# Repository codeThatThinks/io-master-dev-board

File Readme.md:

# io-master-dev-board

A dev board for continuing development of the I/O Master.

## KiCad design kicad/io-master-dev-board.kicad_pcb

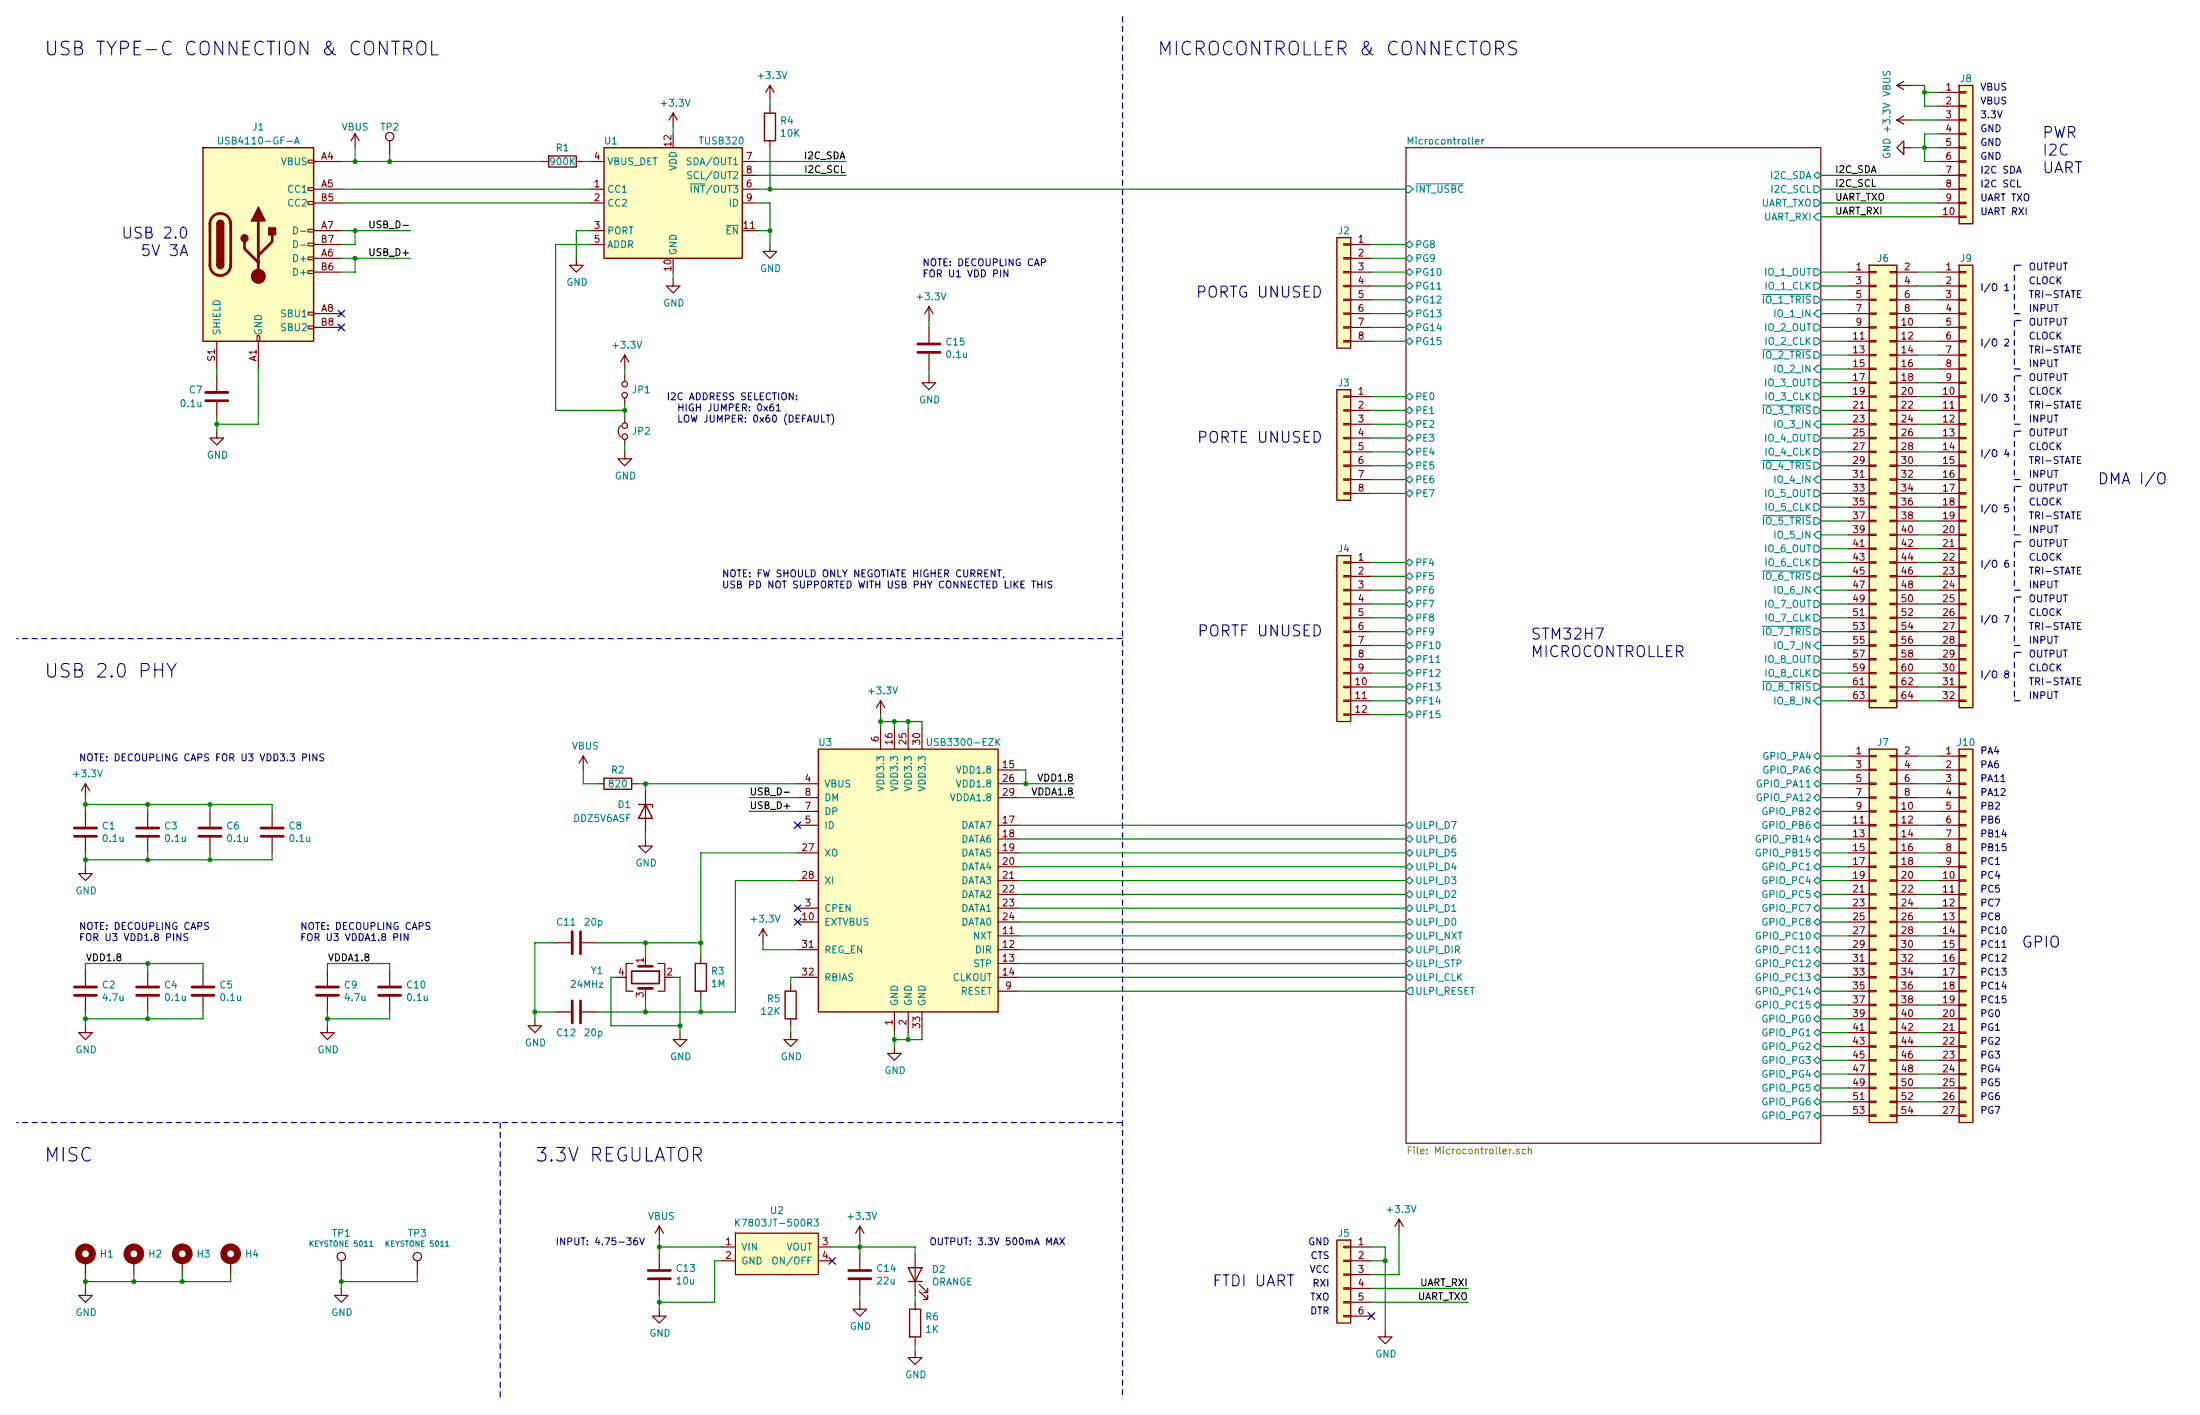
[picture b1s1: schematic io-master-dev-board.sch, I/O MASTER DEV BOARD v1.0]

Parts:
C1, C3, C4, C5, C6, C7, C8, C10, C15: 0.1u; C_0603_1608Metric
C2, C9: 4.7u; C_0805_2012Metric
C11, C12: 20p; C_0603_1608Metric
C13: 10u; C_0805_2012Metric
C14: 22u; C_1210_3225Metric
D1: DDZ5V6ASF; D_SOD-323F
D2: ORANGE; LED_0603_1608Metric
H1, H2, H3, H4: M3; MountingHole_3.2mm_M3_Pad
J1: USB4110-GF-A; USB_C_Receptable_GCT_USB4110
J2, J3: Conn_01x08; PinHeader_1x08_P2.54mm_Vertical
J4: Conn_01x12; PinHeader_1x12_P2.54mm_Vertical
J5: UART; PinHeader_1x06_P2.54mm_Horizontal
J6: Conn_02x32_Odd_Even; PinHeader_2x32_P1.27mm_Vertical
J7: Conn_02x27_Odd_Even; PinHeader_2x27_P1.27mm_Vertical
J8: Conn_01x10; PinHeader_1x10_P1.27mm_Vertical
J9: Conn_01x32; PinHeader_1x32_P1.27mm_Vertical
J10: Conn_01x27; PinHeader_1x27_P1.27mm_Vertical
JP1: Jumper_NO_Small; R_0603_1608Metric
JP2: Jumper_NC_Small; R_0603_1608Metric
R1: 900K; R_0603_1608Metric
R2: 820; R_0603_1608Metric
R3: 1M; R_0603_1608Metric
R4: 10K; R_0603_1608Metric
R5: 12K; R_0603_1608Metric
R6: 1K; R_0603_1608Metric
TP1, TP3: GND; TestPoint_Keystone_5010-5014_Multipurpose
TP2: VBUS; TestPoint_Pad_D1.0mm
U1: TUSB320; Texas_X2QFN-12_1.6x1.6mm_P0.4mm
U2: K7803JT-500R3; DCDC_Module_K78xxJT-500R3
U3: USB3300-EZK; QFN-32-1EP_5x5mm_P0.5mm_EP3.45x3.45mm
Y1: 24MHz; Crystal_SMD_Murata_XRCGB

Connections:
+3V3: C1.1, C3.1, C6.1, C8.1, C14.1, C15.1, D2.2 (A), J5.3, J8.3, JP1.2, R4.1, U1.12 (VDD), U2.3 (VOUT), U3.6 (VDD3.3), U3.16 (VDD3.3), U3.25 (VDD3.3), U3.30 (VDD3.3), U3.31 (REG_EN); also elsewhere on the board
/I2C_SCL: J8.8, U1.8 (SCL/OUT2); also elsewhere on the board
/I2C_SDA: J8.7, U1.7 (SDA/OUT1); also elsewhere on the board
/Microcontroller/GPIO_PA4: J7.1; also elsewhere on the board
/Microcontroller/GPIO_PA6: J7.3; also elsewhere on the board
/Microcontroller/GPIO_PA11: J7.5; also elsewhere on the board
/Microcontroller/GPIO_PA12: J7.7; also elsewhere on the board
/Microcontroller/GPIO_PB2: J7.9; also elsewhere on the board
/Microcontroller/GPIO_PB6: J7.11; also elsewhere on the board
/Microcontroller/GPIO_PB14: J7.13; also elsewhere on the board
/Microcontroller/GPIO_PB15: J7.15; also elsewhere on the board
/Microcontroller/GPIO_PC1: J7.17; also elsewhere on the board
/Microcontroller/GPIO_PC4: J7.19; also elsewhere on the board
/Microcontroller/GPIO_PC5: J7.21; also elsewhere on the board
/Microcontroller/GPIO_PC7: J7.23; also elsewhere on the board
/Microcontroller/GPIO_PC8: J7.25; also elsewhere on the board
/Microcontroller/GPIO_PC10: J7.27; also elsewhere on the board
/Microcontroller/GPIO_PC11: J7.29; also elsewhere on the board
/Microcontroller/GPIO_PC12: J7.31; also elsewhere on the board
/Microcontroller/GPIO_PC13: J7.33; also elsewhere on the board
/Microcontroller/GPIO_PC14: J7.35; also elsewhere on the board
/Microcontroller/GPIO_PC15: J7.37; also elsewhere on the board
/Microcontroller/GPIO_PG0: J7.39; also elsewhere on the board
/Microcontroller/GPIO_PG1: J7.41; also elsewhere on the board
/Microcontroller/GPIO_PG2: J7.43; also elsewhere on the board
/Microcontroller/GPIO_PG3: J7.45; also elsewhere on the board
/Microcontroller/GPIO_PG4: J7.47; also elsewhere on the board
/Microcontroller/GPIO_PG5: J7.49; also elsewhere on the board
/Microcontroller/GPIO_PG6: J7.51; also elsewhere on the board
/Microcontroller/GPIO_PG7: J7.53; also elsewhere on the board
/Microcontroller/IO_1_CLK: J6.3; also elsewhere on the board
/Microcontroller/IO_1_IN: J6.7; also elsewhere on the board
/Microcontroller/IO_1_OUT: J6.1; also elsewhere on the board
/Microcontroller/IO_2_CLK: J6.11; also elsewhere on the board
/Microcontroller/IO_2_IN: J6.15; also elsewhere on the board
/Microcontroller/IO_2_OUT: J6.9; also elsewhere on the board
/Microcontroller/IO_3_CLK: J6.19; also elsewhere on the board
/Microcontroller/IO_3_IN: J6.23; also elsewhere on the board
/Microcontroller/IO_3_OUT: J6.17; also elsewhere on the board
/Microcontroller/IO_4_CLK: J6.27; also elsewhere on the board
/Microcontroller/IO_4_IN: J6.31; also elsewhere on the board
/Microcontroller/IO_4_OUT: J6.25; also elsewhere on the board
/Microcontroller/IO_5_CLK: J6.35; also elsewhere on the board
/Microcontroller/IO_5_IN: J6.39; also elsewhere on the board
/Microcontroller/IO_5_OUT: J6.33; also elsewhere on the board
/Microcontroller/IO_6_CLK: J6.43; also elsewhere on the board
/Microcontroller/IO_6_IN: J6.47; also elsewhere on the board
/Microcontroller/IO_6_OUT: J6.41; also elsewhere on the board
/Microcontroller/IO_7_CLK: J6.51; also elsewhere on the board
/Microcontroller/IO_7_IN: J6.55; also elsewhere on the board
/Microcontroller/IO_7_OUT: J6.49; also elsewhere on the board
/Microcontroller/IO_8_CLK: J6.59; also elsewhere on the board
/Microcontroller/IO_8_IN: J6.63; also elsewhere on the board
/Microcontroller/IO_8_OUT: J6.57; also elsewhere on the board
/Microcontroller/PE0: J3.1; also elsewhere on the board
/Microcontroller/PE1: J3.2; also elsewhere on the board
/Microcontroller/PE2: J3.3; also elsewhere on the board
/Microcontroller/PE3: J3.4; also elsewhere on the board
/Microcontroller/PE4: J3.5; also elsewhere on the board
/Microcontroller/PE5: J3.6; also elsewhere on the board
/Microcontroller/PE6: J3.7; also elsewhere on the board
/Microcontroller/PE7: J3.8; also elsewhere on the board
/Microcontroller/PF4: J4.1; also elsewhere on the board
/Microcontroller/PF5: J4.2; also elsewhere on the board
/Microcontroller/PF6: J4.3; also elsewhere on the board
/Microcontroller/PF7: J4.4; also elsewhere on the board
/Microcontroller/PF8: J4.5; also elsewhere on the board
/Microcontroller/PF9: J4.6; also elsewhere on the board
/Microcontroller/PF10: J4.7; also elsewhere on the board
/Microcontroller/PF11: J4.8; also elsewhere on the board
/Microcontroller/PF12: J4.9; also elsewhere on the board
/Microcontroller/PF13: J4.10; also elsewhere on the board
/Microcontroller/PF14: J4.11; also elsewhere on the board
/Microcontroller/PF15: J4.12; also elsewhere on the board
/Microcontroller/PG8: J2.1; also elsewhere on the board
/Microcontroller/PG9: J2.2; also elsewhere on the board
/Microcontroller/PG10: J2.3; also elsewhere on the board
/Microcontroller/PG11: J2.4; also elsewhere on the board
/Microcontroller/PG12: J2.5; also elsewhere on the board
/Microcontroller/PG13: J2.6; also elsewhere on the board
/Microcontroller/PG14: J2.7; also elsewhere on the board
/Microcontroller/PG15: J2.8; also elsewhere on the board
/Microcontroller/ULPI_CLK: U3.14 (CLKOUT); also elsewhere on the board
/Microcontroller/ULPI_D0: U3.24 (DATA0); also elsewhere on the board
/Microcontroller/ULPI_D1: U3.23 (DATA1); also elsewhere on the board
/Microcontroller/ULPI_D2: U3.22 (DATA2); also elsewhere on the board
/Microcontroller/ULPI_D3: U3.21 (DATA3); also elsewhere on the board
/Microcontroller/ULPI_D4: U3.20 (DATA4); also elsewhere on the board
/Microcontroller/ULPI_D5: U3.19 (DATA5); also elsewhere on the board
/Microcontroller/ULPI_D6: U3.18 (DATA6); also elsewhere on the board
/Microcontroller/ULPI_D7: U3.17 (DATA7); also elsewhere on the board
/Microcontroller/ULPI_DIR: U3.12 (DIR); also elsewhere on the board
/Microcontroller/ULPI_NXT: U3.11 (NXT); also elsewhere on the board
/Microcontroller/ULPI_RESET: U3.9 (RESET); also elsewhere on the board
/Microcontroller/ULPI_STP: U3.13 (STP); also elsewhere on the board
/Microcontroller/~INT_USBC: R4.2, U1.6 (~INT~/OUT3); also elsewhere on the board
/Microcontroller/~IO_1_TRIS: J6.5; also elsewhere on the board
/Microcontroller/~IO_2_TRIS: J6.13; also elsewhere on the board
/Microcontroller/~IO_3_TRIS: J6.21; also elsewhere on the board
/Microcontroller/~IO_4_TRIS: J6.29; also elsewhere on the board
/Microcontroller/~IO_5_TRIS: J6.37; also elsewhere on the board
/Microcontroller/~IO_6_TRIS: J6.45; also elsewhere on the board
/Microcontroller/~IO_7_TRIS: J6.53; also elsewhere on the board
/Microcontroller/~IO_8_TRIS: J6.61; also elsewhere on the board
/UART_RXI: J5.4, J8.10; also elsewhere on the board
/UART_TXO: J5.5, J8.9; also elsewhere on the board
/USB_D+: J1.A6 (D+), J1.B6 (D+), U3.7 (DP)
/USB_D-: J1.A7 (D-), J1.B7 (D-), U3.8 (DM)
/VDD1.8: C2.1, C4.1, C5.1, U3.15 (VDD1.8), U3.26 (VDD1.8)
/VDDA1.8: C9.1, C10.1, U3.29 (VDDA1.8)
GND: C1.2, C2.2, C3.2, C4.2, C5.2, C6.2, C7.1, C8.2, C9.2, C10.2, C11.2, C12.2, C13.2, C14.2, C15.2, D1.2 (A), H1.1, H2.1, H3.1, H4.1, J1.A1 (GND), J1.A12 (GND), J1.B1 (GND), J1.B12 (GND), J5.1, J5.2, J8.4, J8.5, J8.6, JP2.1, R5.2, R6.2, TP1.1, TP3.1, U1.3 (PORT), U1.9 (ID), U1.10 (GND), U1.11 (~EN), U2.2 (GND), U3.1 (GND), U3.2 (GND), U3.33 (GND), Y1.2, Y1.4; also elsewhere on the board
unnamed: C7.2, J1.S1 (SHIELD)
unnamed: C11.1, R3.1, U3.27 (XO), Y1.1
unnamed: C12.1, R3.2, U3.28 (XI), Y1.3
unnamed: D1.1 (K), R2.1, U3.4 (VBUS)
unnamed: D2.1 (K), R6.1
unnamed: J1.A5 (CC1), U1.1 (CC1)
unnamed: J1.B5 (CC2), U1.2 (CC2)
unnamed: J6.2, J9.1
unnamed: J6.4, J9.2
unnamed: J6.6, J9.3
unnamed: J6.8, J9.4
unnamed: J6.10, J9.5
unnamed: J6.12, J9.6
unnamed: J6.14, J9.7
unnamed: J6.16, J9.8
unnamed: J6.18, J9.9
unnamed: J6.20, J9.10
unnamed: J6.22, J9.11
unnamed: J6.24, J9.12
unnamed: J6.26, J9.13
unnamed: J6.28, J9.14
unnamed: J6.30, J9.15
unnamed: J6.32, J9.16
unnamed: J6.34, J9.17
unnamed: J6.36, J9.18
unnamed: J6.38, J9.19
unnamed: J6.40, J9.20
unnamed: J6.42, J9.21
unnamed: J6.44, J9.22
unnamed: J6.46, J9.23
unnamed: J6.48, J9.24
unnamed: J6.50, J9.25
unnamed: J6.52, J9.26
unnamed: J6.54, J9.27
unnamed: J6.56, J9.28
unnamed: J6.58, J9.29
unnamed: J6.60, J9.30
unnamed: J6.62, J9.31
unnamed: J6.64, J9.32
unnamed: J7.2, J10.1
unnamed: J7.4, J10.2
unnamed: J7.6, J10.3
unnamed: J7.8, J10.4
unnamed: J7.10, J10.5
unnamed: J7.12, J10.6
unnamed: J7.14, J10.7
unnamed: J7.16, J10.8
unnamed: J7.18, J10.9
unnamed: J7.20, J10.10
unnamed: J7.22, J10.11
unnamed: J7.24, J10.12
unnamed: J7.26, J10.13
unnamed: J7.28, J10.14
unnamed: J7.30, J10.15
unnamed: J7.32, J10.16
unnamed: J7.34, J10.17
unnamed: J7.36, J10.18
unnamed: J7.38, J10.19
unnamed: J7.40, J10.20
unnamed: J7.42, J10.21
unnamed: J7.44, J10.22
unnamed: J7.46, J10.23
unnamed: J7.48, J10.24
unnamed: J7.50, J10.25
unnamed: J7.52, J10.26
unnamed: J7.54, J10.27
unnamed: JP1.1, JP2.2, U1.5 (ADDR)
unnamed: R1.1, U1.4 (VBUS_DET)
unnamed: R5.1, U3.32 (RBIAS)
VBUS: C13.1, J1.A4 (VBUS), J1.A9 (VBUS), J1.B4 (VBUS), J1.B9 (VBUS), J8.1, J8.2, R1.2, R2.2, TP2.1, U2.1 (VIN)

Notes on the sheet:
NOTE: DECOUPLING CAPS FOR U3 VDD1.8 PINS
NOTE: DECOUPLING CAPS FOR U3 VDD3.3 PINS
NOTE: DECOUPLING CAPS FOR U3 VDDA1.8 PIN
USB TYPE-C CONNECTION & CONTROL
USB 2.0 5V 3A
3.3V REGULATOR
I2C ADDRESS SELECTION: HIGH JUMPER: 0x61 LOW JUMPER: 0x60 (DEFAULT)
NOTE: DECOUPLING CAP FOR U1 VDD PIN
INPUT: 4.75-36V
OUTPUT: 3.3V 500mA MAX
STM32H7 MICROCONTROLLER
USB 2.0 PHY
MISC
MICROCONTROLLER & CONNECTORS
PWR I2C UART
DMA I/O
VBUS
3.3V
GND
I2C SDA
I2C SCL
UART TXO
UART RXI
I/O 1
OUTPUT
CLOCK
TRI-STATE
INPUT
I/O 2
I/O 3
I/O 4
I/O 5
I/O 6
I/O 7
I/O 8
GPIO
PA4
PA6
PA11
PA12

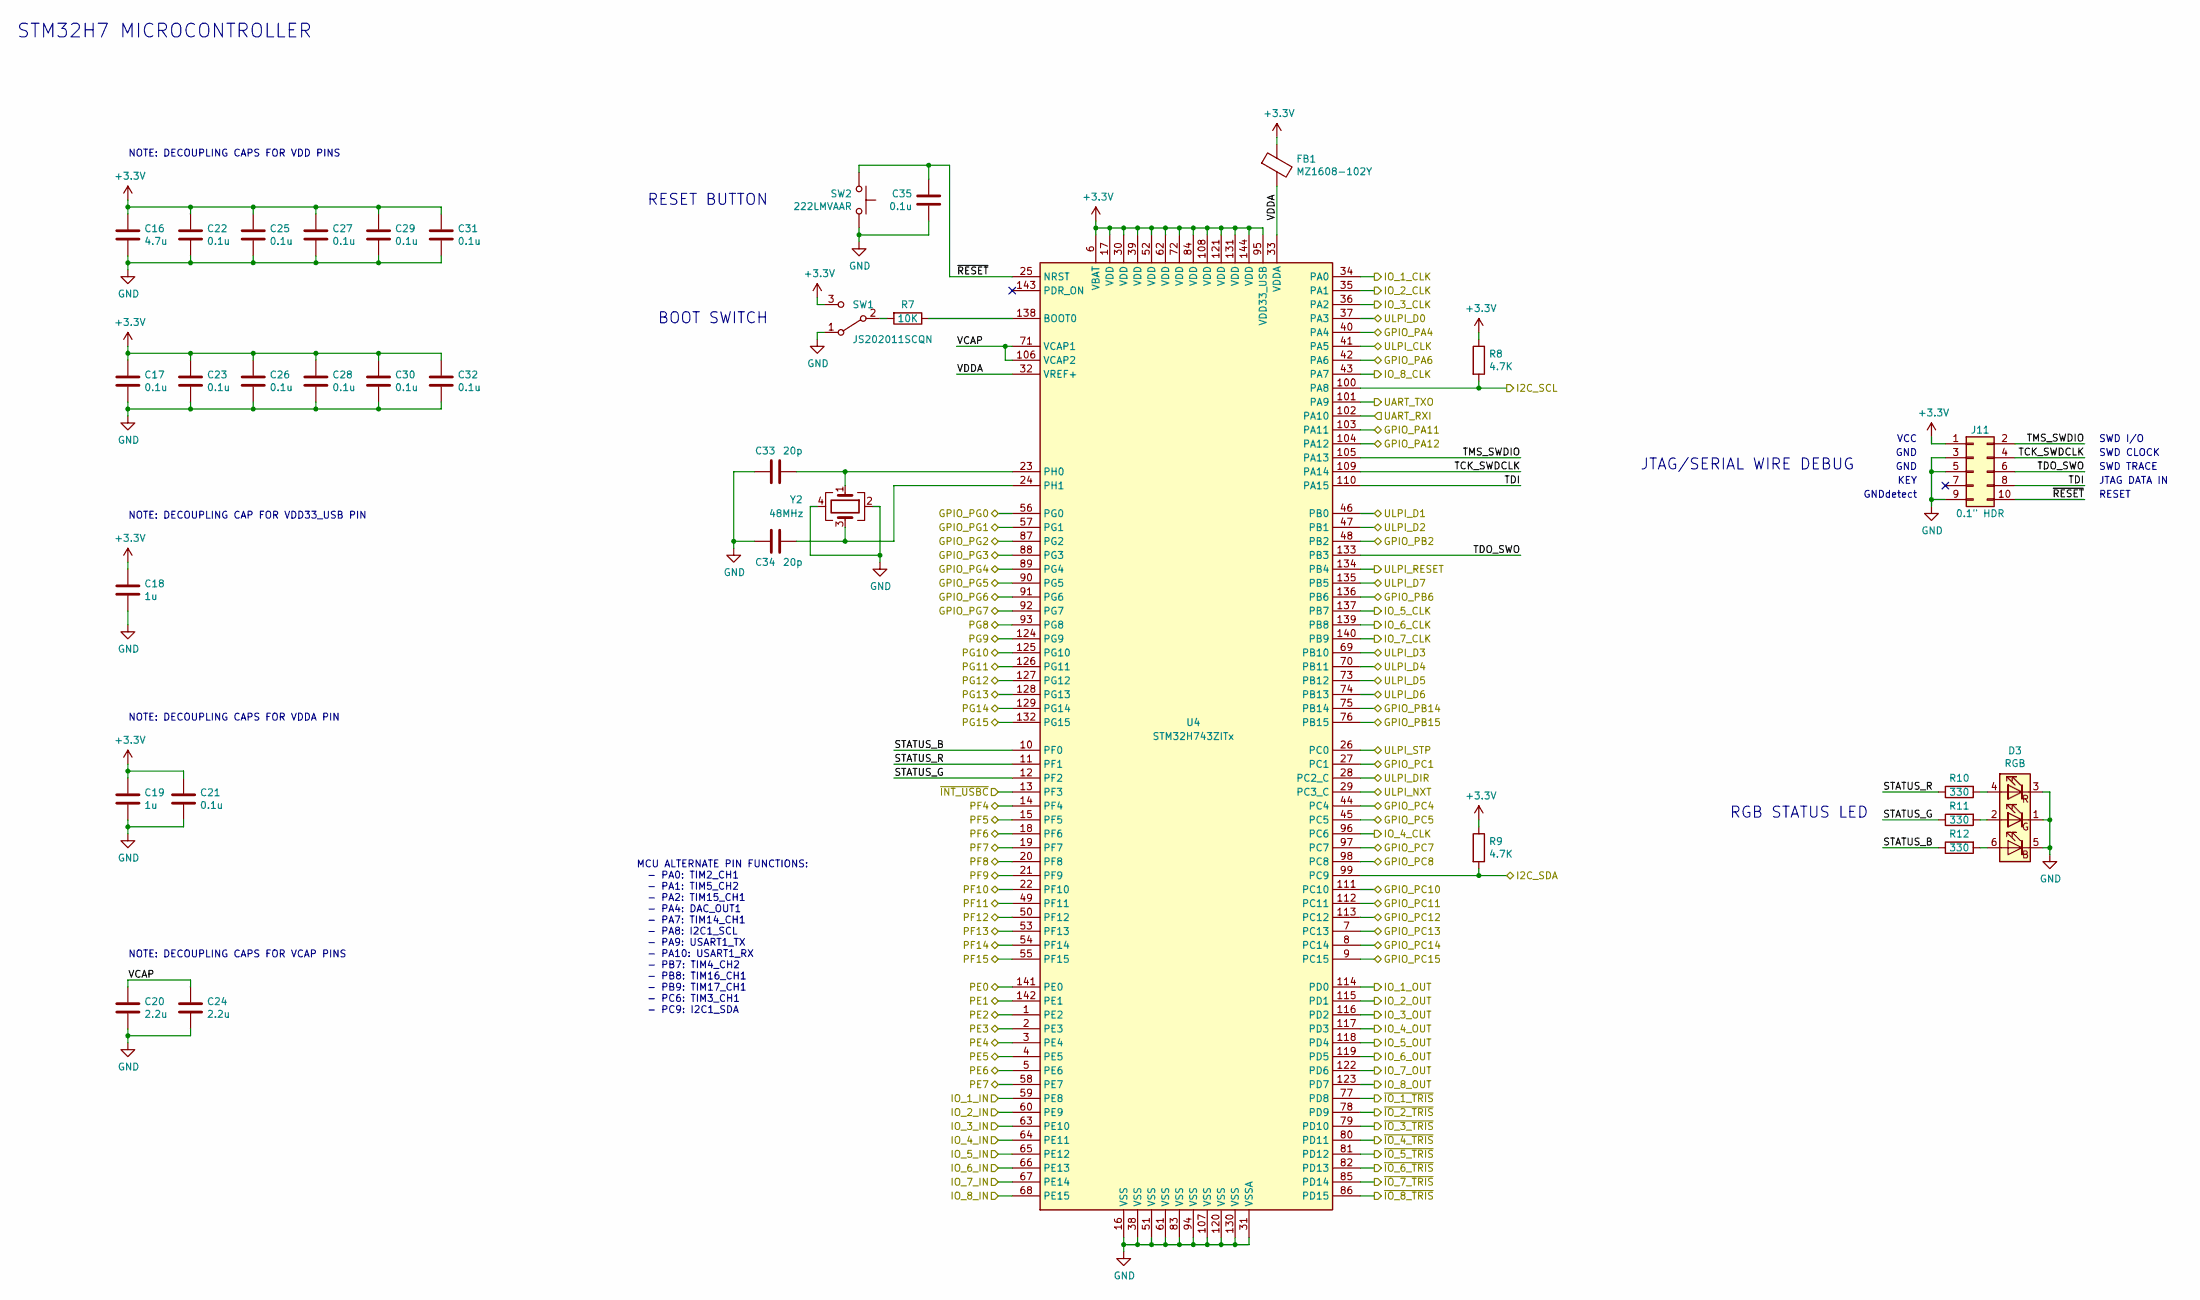
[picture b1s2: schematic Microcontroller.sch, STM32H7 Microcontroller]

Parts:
C16: 4.7u; C_0805_2012Metric
C17, C21, C22, C23, C25, C26, C27, C28, C29, C30, C31, C32, C35: 0.1u; C_0603_1608Metric
C18, C19: 1u; C_0603_1608Metric
C20, C24: 2.2u; C_0805_2012Metric
C33, C34: 20p; C_0603_1608Metric
D3: RGB; LED_Everlight_19-337C
FB1: MZ1608-102Y; R_0603_1608Metric
J11: 0.1\" HDR; PinSocket_2x05_P2.54mm_Vertical
R7: 10K; R_0603_1608Metric
R8, R9: 4.7K; R_0603_1608Metric
R10, R11, R12: 330; R_0603_1608Metric
SW1: JS202011SCQN; SW_DPDT_CK_JS202011SCQN
SW2: 222LMVAAR; SW_Push_CTS_222LMVA
U4: STM32H743ZITx; LQFP-144_20x20mm_P0.5mm
Y2: 48MHz; Crystal_SMD_Murata_XRCGB

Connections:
+3V3: C16.1, C17.1, C18.1, C19.1, C21.1, C22.1, C23.1, C25.1, C26.1, C27.1, C28.1, C29.1, C30.1, C31.1, C32.1, FB1.1, J11.1, R8.1, R9.1, SW1.3 (C), U4.6 (VBAT), U4.17 (VDD), U4.30 (VDD), U4.39 (VDD), U4.52 (VDD), U4.62 (VDD), U4.72 (VDD), U4.84 (VDD), U4.95 (VDD33_USB), U4.108 (VDD), U4.121 (VDD), U4.131 (VDD), U4.144 (VDD); also elsewhere on the board
/I2C_SCL: R8.2, U4.100 (PA8); also elsewhere on the board
/I2C_SDA: R9.2, U4.99 (PC9); also elsewhere on the board
/Microcontroller/GPIO_PA4: U4.40 (PA4); also elsewhere on the board
/Microcontroller/GPIO_PA6: U4.42 (PA6); also elsewhere on the board
/Microcontroller/GPIO_PA11: U4.103 (PA11); also elsewhere on the board
/Microcontroller/GPIO_PA12: U4.104 (PA12); also elsewhere on the board
/Microcontroller/GPIO_PB2: U4.48 (PB2); also elsewhere on the board
/Microcontroller/GPIO_PB6: U4.136 (PB6); also elsewhere on the board
/Microcontroller/GPIO_PB14: U4.75 (PB14); also elsewhere on the board
/Microcontroller/GPIO_PB15: U4.76 (PB15); also elsewhere on the board
/Microcontroller/GPIO_PC1: U4.27 (PC1); also elsewhere on the board
/Microcontroller/GPIO_PC4: U4.44 (PC4); also elsewhere on the board
/Microcontroller/GPIO_PC5: U4.45 (PC5); also elsewhere on the board
/Microcontroller/GPIO_PC7: U4.97 (PC7); also elsewhere on the board
/Microcontroller/GPIO_PC8: U4.98 (PC8); also elsewhere on the board
/Microcontroller/GPIO_PC10: U4.111 (PC10); also elsewhere on the board
/Microcontroller/GPIO_PC11: U4.112 (PC11); also elsewhere on the board
/Microcontroller/GPIO_PC12: U4.113 (PC12); also elsewhere on the board
/Microcontroller/GPIO_PC13: U4.7 (PC13); also elsewhere on the board
/Microcontroller/GPIO_PC14: U4.8 (PC14); also elsewhere on the board
/Microcontroller/GPIO_PC15: U4.9 (PC15); also elsewhere on the board
/Microcontroller/GPIO_PG0: U4.56 (PG0); also elsewhere on the board
/Microcontroller/GPIO_PG1: U4.57 (PG1); also elsewhere on the board
/Microcontroller/GPIO_PG2: U4.87 (PG2); also elsewhere on the board
/Microcontroller/GPIO_PG3: U4.88 (PG3); also elsewhere on the board
/Microcontroller/GPIO_PG4: U4.89 (PG4); also elsewhere on the board
/Microcontroller/GPIO_PG5: U4.90 (PG5); also elsewhere on the board
/Microcontroller/GPIO_PG6: U4.91 (PG6); also elsewhere on the board
/Microcontroller/GPIO_PG7: U4.92 (PG7); also elsewhere on the board
/Microcontroller/IO_1_CLK: U4.34 (PA0); also elsewhere on the board
/Microcontroller/IO_1_IN: U4.59 (PE8); also elsewhere on the board
/Microcontroller/IO_1_OUT: U4.114 (PD0); also elsewhere on the board
/Microcontroller/IO_2_CLK: U4.35 (PA1); also elsewhere on the board
/Microcontroller/IO_2_IN: U4.60 (PE9); also elsewhere on the board
/Microcontroller/IO_2_OUT: U4.115 (PD1); also elsewhere on the board
/Microcontroller/IO_3_CLK: U4.36 (PA2); also elsewhere on the board
/Microcontroller/IO_3_IN: U4.63 (PE10); also elsewhere on the board
/Microcontroller/IO_3_OUT: U4.116 (PD2); also elsewhere on the board
/Microcontroller/IO_4_CLK: U4.96 (PC6); also elsewhere on the board
/Microcontroller/IO_4_IN: U4.64 (PE11); also elsewhere on the board
/Microcontroller/IO_4_OUT: U4.117 (PD3); also elsewhere on the board
/Microcontroller/IO_5_CLK: U4.137 (PB7); also elsewhere on the board
/Microcontroller/IO_5_IN: U4.65 (PE12); also elsewhere on the board
/Microcontroller/IO_5_OUT: U4.118 (PD4); also elsewhere on the board
/Microcontroller/IO_6_CLK: U4.139 (PB8); also elsewhere on the board
/Microcontroller/IO_6_IN: U4.66 (PE13); also elsewhere on the board
/Microcontroller/IO_6_OUT: U4.119 (PD5); also elsewhere on the board
/Microcontroller/IO_7_CLK: U4.140 (PB9); also elsewhere on the board
/Microcontroller/IO_7_IN: U4.67 (PE14); also elsewhere on the board
/Microcontroller/IO_7_OUT: U4.122 (PD6); also elsewhere on the board
/Microcontroller/IO_8_CLK: U4.43 (PA7); also elsewhere on the board
/Microcontroller/IO_8_IN: U4.68 (PE15); also elsewhere on the board
/Microcontroller/IO_8_OUT: U4.123 (PD7); also elsewhere on the board
/Microcontroller/PE0: U4.141 (PE0); also elsewhere on the board
/Microcontroller/PE1: U4.142 (PE1); also elsewhere on the board
/Microcontroller/PE2: U4.1 (PE2); also elsewhere on the board
/Microcontroller/PE3: U4.2 (PE3); also elsewhere on the board
/Microcontroller/PE4: U4.3 (PE4); also elsewhere on the board
/Microcontroller/PE5: U4.4 (PE5); also elsewhere on the board
/Microcontroller/PE6: U4.5 (PE6); also elsewhere on the board
/Microcontroller/PE7: U4.58 (PE7); also elsewhere on the board
/Microcontroller/PF4: U4.14 (PF4); also elsewhere on the board
/Microcontroller/PF5: U4.15 (PF5); also elsewhere on the board
/Microcontroller/PF6: U4.18 (PF6); also elsewhere on the board
/Microcontroller/PF7: U4.19 (PF7); also elsewhere on the board
/Microcontroller/PF8: U4.20 (PF8); also elsewhere on the board
/Microcontroller/PF9: U4.21 (PF9); also elsewhere on the board
/Microcontroller/PF10: U4.22 (PF10); also elsewhere on the board
/Microcontroller/PF11: U4.49 (PF11); also elsewhere on the board
/Microcontroller/PF12: U4.50 (PF12); also elsewhere on the board
/Microcontroller/PF13: U4.53 (PF13); also elsewhere on the board
/Microcontroller/PF14: U4.54 (PF14); also elsewhere on the board
/Microcontroller/PF15: U4.55 (PF15); also elsewhere on the board
/Microcontroller/PG8: U4.93 (PG8); also elsewhere on the board
/Microcontroller/PG9: U4.124 (PG9); also elsewhere on the board
/Microcontroller/PG10: U4.125 (PG10); also elsewhere on the board
/Microcontroller/PG11: U4.126 (PG11); also elsewhere on the board
/Microcontroller/PG12: U4.127 (PG12); also elsewhere on the board
/Microcontroller/PG13: U4.128 (PG13); also elsewhere on the board
/Microcontroller/PG14: U4.129 (PG14); also elsewhere on the board
/Microcontroller/PG15: U4.132 (PG15); also elsewhere on the board
/Microcontroller/STATUS_B: R12.1, U4.10 (PF0)
/Microcontroller/STATUS_G: R11.1, U4.12 (PF2)
/Microcontroller/STATUS_R: R10.1, U4.11 (PF1)
/Microcontroller/TCK_SWDCLK: J11.4, U4.109 (PA14)
/Microcontroller/TDI: J11.8, U4.110 (PA15)
/Microcontroller/TDO_SWO: J11.6, U4.133 (PB3)
/Microcontroller/TMS_SWDIO: J11.2, U4.105 (PA13)
/Microcontroller/ULPI_CLK: U4.41 (PA5); also elsewhere on the board
/Microcontroller/ULPI_D0: U4.37 (PA3); also elsewhere on the board
/Microcontroller/ULPI_D1: U4.46 (PB0); also elsewhere on the board
/Microcontroller/ULPI_D2: U4.47 (PB1); also elsewhere on the board
/Microcontroller/ULPI_D3: U4.69 (PB10); also elsewhere on the board
/Microcontroller/ULPI_D4: U4.70 (PB11); also elsewhere on the board
/Microcontroller/ULPI_D5: U4.73 (PB12); also elsewhere on the board
/Microcontroller/ULPI_D6: U4.74 (PB13); also elsewhere on the board
/Microcontroller/ULPI_D7: U4.135 (PB5); also elsewhere on the board
/Microcontroller/ULPI_DIR: U4.28 (PC2_C); also elsewhere on the board
/Microcontroller/ULPI_NXT: U4.29 (PC3_C); also elsewhere on the board
/Microcontroller/ULPI_RESET: U4.134 (PB4); also elsewhere on the board
/Microcontroller/ULPI_STP: U4.26 (PC0); also elsewhere on the board
/Microcontroller/VCAP: C20.1, C24.1, U4.71 (VCAP1), U4.106 (VCAP2)
/Microcontroller/VDDA: FB1.2, U4.32 (VREF+), U4.33 (VDDA)
/Microcontroller/~INT_USBC: U4.13 (PF3); also elsewhere on the board
/Microcontroller/~IO_1_TRIS: U4.77 (PD8); also elsewhere on the board
/Microcontroller/~IO_2_TRIS: U4.78 (PD9); also elsewhere on the board
/Microcontroller/~IO_3_TRIS: U4.79 (PD10); also elsewhere on the board
/Microcontroller/~IO_4_TRIS: U4.80 (PD11); also elsewhere on the board
/Microcontroller/~IO_5_TRIS: U4.81 (PD12); also elsewhere on the board
/Microcontroller/~IO_6_TRIS: U4.82 (PD13); also elsewhere on the board
/Microcontroller/~IO_7_TRIS: U4.85 (PD14); also elsewhere on the board
/Microcontroller/~IO_8_TRIS: U4.86 (PD15); also elsewhere on the board
/Microcontroller/~RESET: C35.1, J11.10, SW2.2, U4.25 (NRST)
/UART_RXI: U4.102 (PA10); also elsewhere on the board
/UART_TXO: U4.101 (PA9); also elsewhere on the board
GND: C16.2, C17.2, C18.2, C19.2, C20.2, C21.2, C22.2, C23.2, C24.2, C25.2, C26.2, C27.2, C28.2, C29.2, C30.2, C31.2, C32.2, C33.2, C34.2, C35.2, D3.1 (GK), D3.3 (RK), D3.5 (BK), J11.3, J11.5, J11.9, SW1.1 (A), SW2.1, U4.16 (VSS), U4.31 (VSSA), U4.38 (VSS), U4.51 (VSS), U4.61 (VSS), U4.83 (VSS), U4.94 (VSS), U4.107 (VSS), U4.120 (VSS), U4.130 (VSS), Y2.2, Y2.4; also elsewhere on the board
unnamed: C33.1, U4.23 (PH0), Y2.1
unnamed: C34.1, U4.24 (PH1), Y2.3
unnamed: D3.2 (GA), R11.2
unnamed: D3.4 (RA), R10.2
unnamed: D3.6 (BA), R12.2
unnamed: R7.1, U4.138 (BOOT0)
unnamed: R7.2, SW1.2 (B)

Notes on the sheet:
STM32H7 MICROCONTROLLER
JTAG/SERIAL WIRE DEBUG
SWD I/O
SWD CLOCK
SWD TRACE
JTAG DATA IN
RESET
VCC
GND
KEY
GNDdetect
NOTE: DECOUPLING CAPS FOR VDDA PIN
NOTE: DECOUPLING CAPS FOR VDD PINS
NOTE: DECOUPLING CAP FOR VDD33_USB PIN
BOOT SWITCH
RGB STATUS LED
RESET BUTTON
NOTE: DECOUPLING CAPS FOR VCAP PINS
MCU ALTERNATE PIN FUNCTIONS: - PA0: TIM2_CH1 - PA1: TIM5_CH2 - PA2: TIM15_CH1 - PA4: DAC_OUT1 - PA7: TIM14_CH1 - PA8: I2C1_SCL - PA9: USART1_TX - PA10: USART1_RX - PB7: TIM4_CH2 - PB8: TIM16_CH1 - PB9: TIM17_CH1 - PC6: TIM3_CH1 - PC9: I2C1_SDA

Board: 2 copper layers, 79 parts (0 on the bottom side), 198 nets, no tracks yet.

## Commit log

2020-12-06 Modify I/O Master v1.0 schematic
2021-12-11 WIP board layout
